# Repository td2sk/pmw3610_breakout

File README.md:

PMW3610 breakout board

[Preview](https://kicanvas.org/?github=https%3A%2F%2Fgithub.com%2Ftd2sk%2Fpmw3610_breakout) by [KiCanvas](https://kicanvas.org/)

## Status

WIP 動作未確認

## LICENSE

CC-BY-4.0

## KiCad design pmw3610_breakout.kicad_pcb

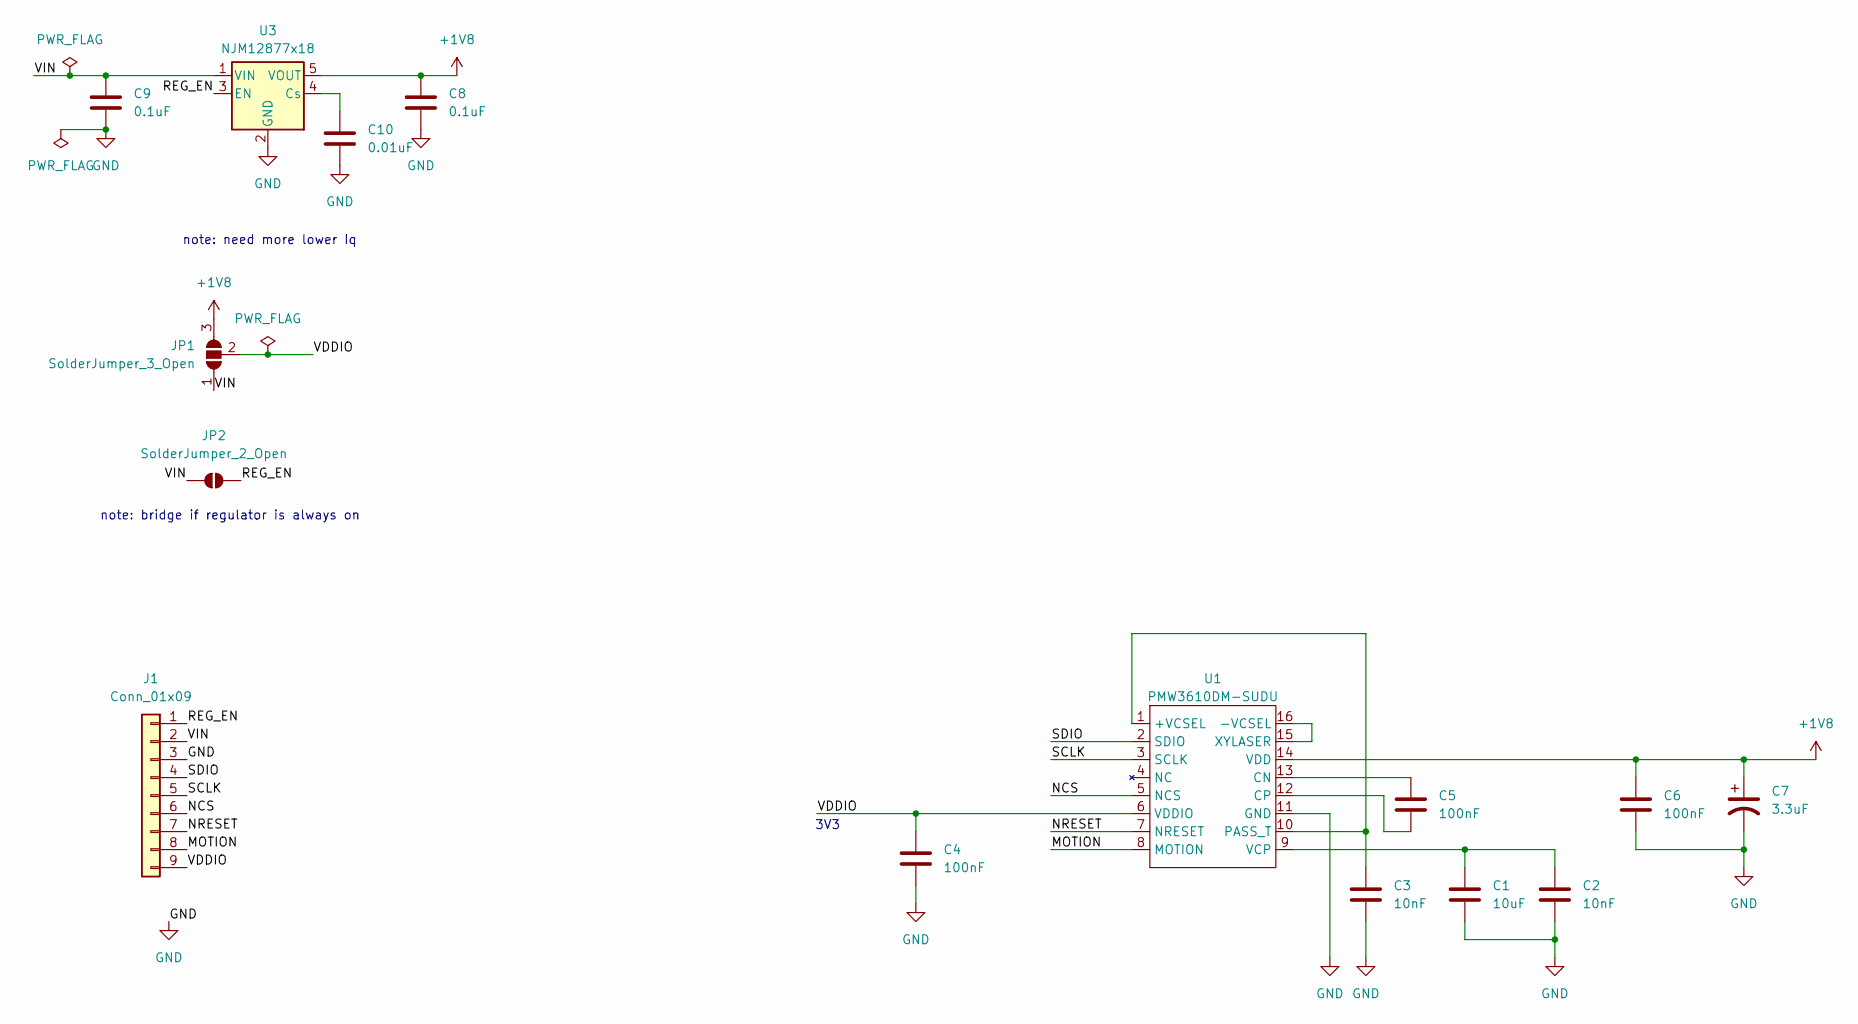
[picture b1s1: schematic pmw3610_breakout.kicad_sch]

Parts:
C1: 10uF; C_0603_1608Metric_Pad1.08x0.95mm_HandSolder
C2, C3: 10nF; C_0603_1608Metric_Pad1.08x0.95mm_HandSolder
C4, C5, C6: 100nF; C_0603_1608Metric_Pad1.08x0.95mm_HandSolder
C7: 3.3uF; C_0603_1608Metric_Pad1.08x0.95mm_HandSolder
C8, C9: 0.1uF; C_0603_1608Metric_Pad1.08x0.95mm_HandSolder
C10: 0.01uF; C_0603_1608Metric_Pad1.08x0.95mm_HandSolder
J1: Conn_01x09; PinHeader_1x09_P2.54mm_Vertical
JP1: SolderJumper_3_Open; SolderJumper-3_P1.3mm_Open_RoundedPad1.0x1.5mm
JP2: SolderJumper_2_Open; SolderJumper-2_P1.3mm_Open_RoundedPad1.0x1.5mm
U1: PMW3610DM-SUDU
U3: NJM12877x18; SOT-23-5

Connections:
+1V8: C6.1, C7.1, C8.1, JP1.3 (B), U1.14 (VDD), U3.5 (VOUT)
/MOTION: J1.8, U1.8 (MOTION)
/NCS: J1.6, U1.5 (NCS)
/NRESET: J1.7, U1.7 (NRESET)
/REG_EN: J1.1, JP2.2 (B), U3.3 (EN)
/SCLK: J1.5, U1.3 (SCLK)
/SDIO: J1.4, U1.2 (SDIO)
/VDDIO: C4.1, J1.9, JP1.2 (C), U1.6 (VDDIO)
/VIN: C9.1, J1.2, JP1.1 (A), JP2.1 (A), U3.1 (VIN)
GND: C1.2, C2.2, C3.2, C4.2, C6.2, C7.2, C8.2, C9.2, C10.2, J1.3, U1.11 (GND), U3.2 (GND)
unnamed: C3.1, U1.1 (+VCSEL), U1.10 (PASS_T)
unnamed: U1.15 (XYLASER), U1.16 (-VCSEL)
unnamed: C5.1, U1.13 (CN)
unnamed: C5.2, U1.12 (CP)
unnamed: C1.1, C2.1, U1.9 (VCP)
unnamed: C10.1, U3.4 (Cs)

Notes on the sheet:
3V3
note: bridge if regulator is always on
note: need more lower Iq

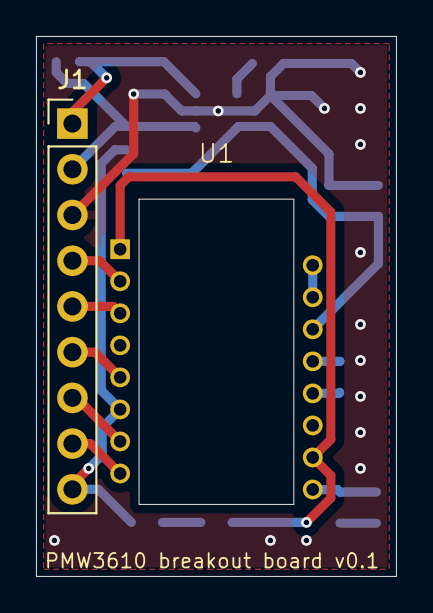
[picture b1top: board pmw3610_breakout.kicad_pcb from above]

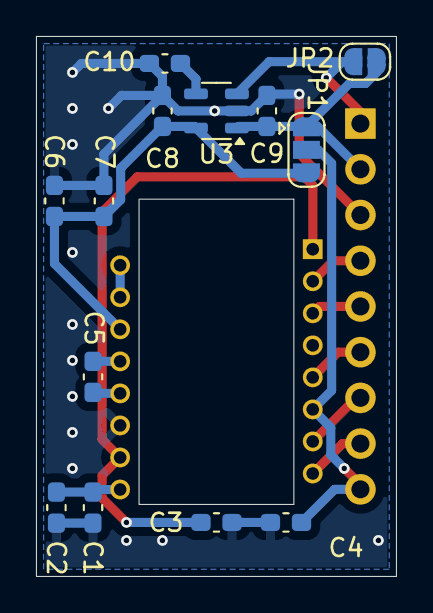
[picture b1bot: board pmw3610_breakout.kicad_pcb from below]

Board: 2 copper layers, 20.0 x 30.0 mm, 15 parts (13 on the bottom side), 16 nets.

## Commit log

2025-02-14 Create LICENSE
2025-02-14 add preview
